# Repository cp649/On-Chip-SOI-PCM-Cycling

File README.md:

# On-Chip-SOI-PCM-Cycling

This is a set of MATLAB scripts to control a Keithley 2200-60-2 and an Agilent function generator 33250 A via USB along with data collection from a Thorlabs DCC1645C-HQ or an AmScope autofocus camera AF205 (via taking screenshots). The file Waveform_main can be used to collect data from an osciloscope (testd on DPO 2014 Tektronix).
The control of the instruments using SCPI code is likely to be easily adaptable to other SCPI controlled instruments. All these scripts serve as an initial point for automating a setup used to test on-chip phase change material electro-thermal (Joule heating) cycling. This code is offered with no guarantees. Additionally, an LTSpice file with the circuit diagram of the system to send large voltage pulses (e.g. > 30 V but below 60 V) is attached. 

Initial attempts to control the Thorlabs camera were based on the code from mdaddysman "https://github.com/mdaddysman/Thorlabs-CMOS-USB-cameras-in-Matlab" but subsequent attempts were based on the from the manual provided by Thorslab (https://www.thorlabs.com/thorProduct.cfm?partNumber=DCC1645C) Thorlab control files are from the link above. Latest version of the main file v2p1.  

Initial building blocks for the control of the Agilent function generator were obtained from the published code by Justinas Lialys on 2 Aug 2020 (https://www.mathworks.com/matlabcentral/answers/574126-agilent-33250a-function-generator-how-to-get-the-waveform-via-serial-port)

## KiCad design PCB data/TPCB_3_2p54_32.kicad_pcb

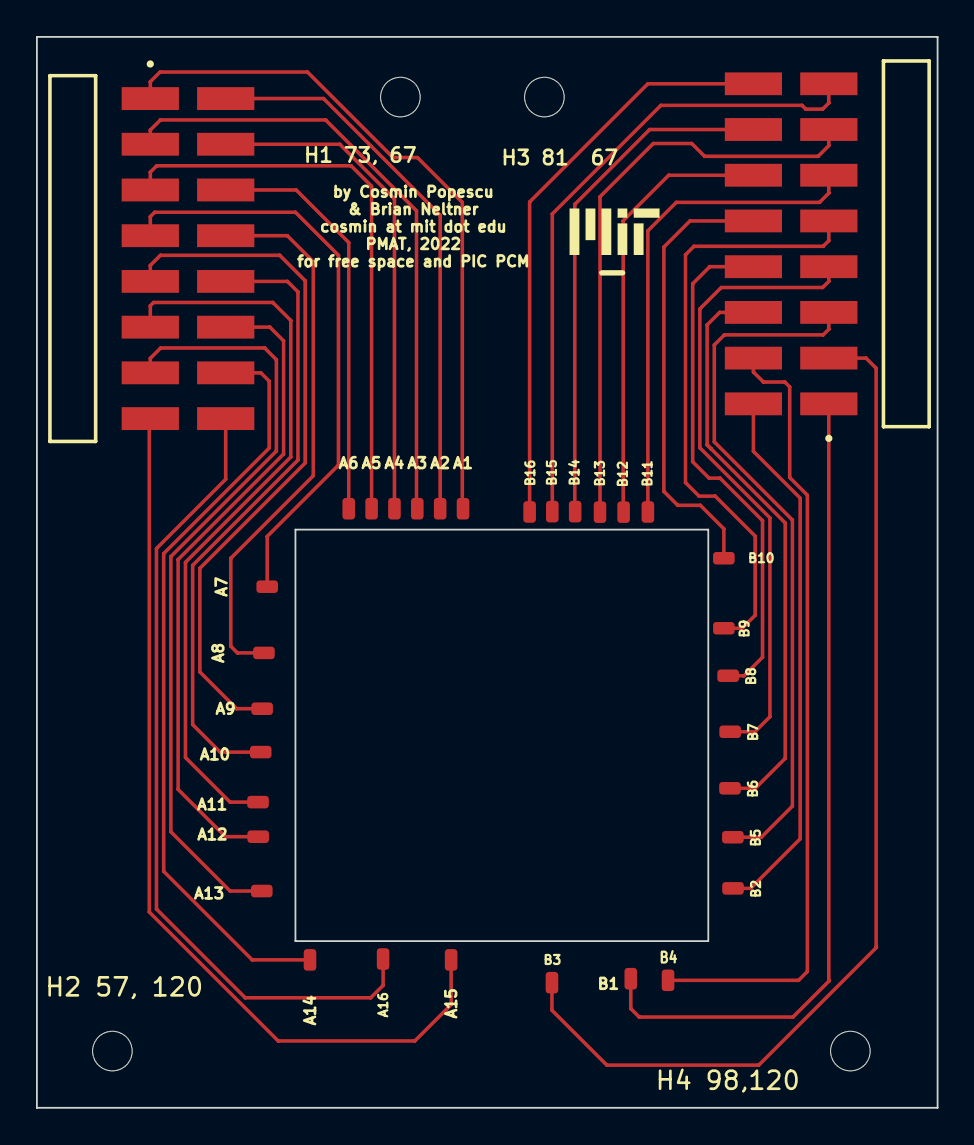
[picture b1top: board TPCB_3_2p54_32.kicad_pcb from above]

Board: 2 copper layers, 50.0 x 59.5 mm, 39 parts (0 on the bottom side), 32 nets.

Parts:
-: LOGO; MIT_5mm
A1, A2, A3, A4, A5, A6, A7, A8, A9, A10, A11, A12, A13, A14, A15, A16: A; SolderWirePad_1x01_SMD_1x2mm
B1, B2, B3, B4, B5, B6, B7, B8, B9, B10, B11, B12, B13, B14, B15, B16: B; SolderWirePad_1x01_SMD_1x2mm
H1 73, 67, H2 57, 120, H3 81  67, H4 98,120: MountingHole; MountingHole_2.2mm_M2
J1, J2: TSM-108-01-F-DH-K; SAMTEC_TSM-108-01-F-DH-K

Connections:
unnamed: A1.1, J1.01
unnamed: A2.1, J1.02
unnamed: A3.1, J1.03
unnamed: A4.1, J1.04
unnamed: A5.1, J1.05
unnamed: A6.1, J1.06
unnamed: A7.1, J1.07
unnamed: A8.1, J1.08
unnamed: A9.1, J1.09
unnamed: A10.1, J1.10
unnamed: A11.1, J1.11
unnamed: A12.1, J1.12
unnamed: A13.1, J1.13
unnamed: A14.1, J1.14
unnamed: A15.1, J1.15
unnamed: A16.1, J1.16
unnamed: B1.1, J2.01
unnamed: B2.1, J2.02
unnamed: B3.1, J2.03
unnamed: B4.1, J2.04
unnamed: B5.1, J2.05
unnamed: B6.1, J2.06
unnamed: B7.1, J2.07
unnamed: B8.1, J2.08
unnamed: B9.1, J2.09
unnamed: B10.1, J2.10
unnamed: B11.1, J2.11
unnamed: B12.1, J2.12
unnamed: B13.1, J2.13
unnamed: B14.1, J2.14
unnamed: B15.1, J2.15
unnamed: B16.1, J2.16

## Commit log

2023-04-17 Add files via upload
    The Zener diode part 1N4745A was not available as a part in LTSpice so another diode with 16 V breakdown voltage was used in the simulation file.
2023-06-19 Add files via upload
    Support structure for PCB with 2 cm x 2 cm chip.
2023-06-20 Add files via upload
    PCB schematic (use KiCad) and design.
2023-07-05 Update PCM_PulseControl_v2p1.m
    Edited conditions for moving to the next cycle during the cooldown stage (corrected the boolean condition)
2023-07-13 Update InitializeAgilent.m
    Added delay times to increase reliability of agilent initialization.
2023-08-07 Add files via upload
    The resistor and small capacitor are not in the BOM. This is not an endorsement of the products. They are just either the ones we used or close enough to the ones in the actual setup. Please feel fre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
2024-03-28 Update PCM_PulseControl_v2p1.m
    Changed from visa to visadev for smoother operation.
